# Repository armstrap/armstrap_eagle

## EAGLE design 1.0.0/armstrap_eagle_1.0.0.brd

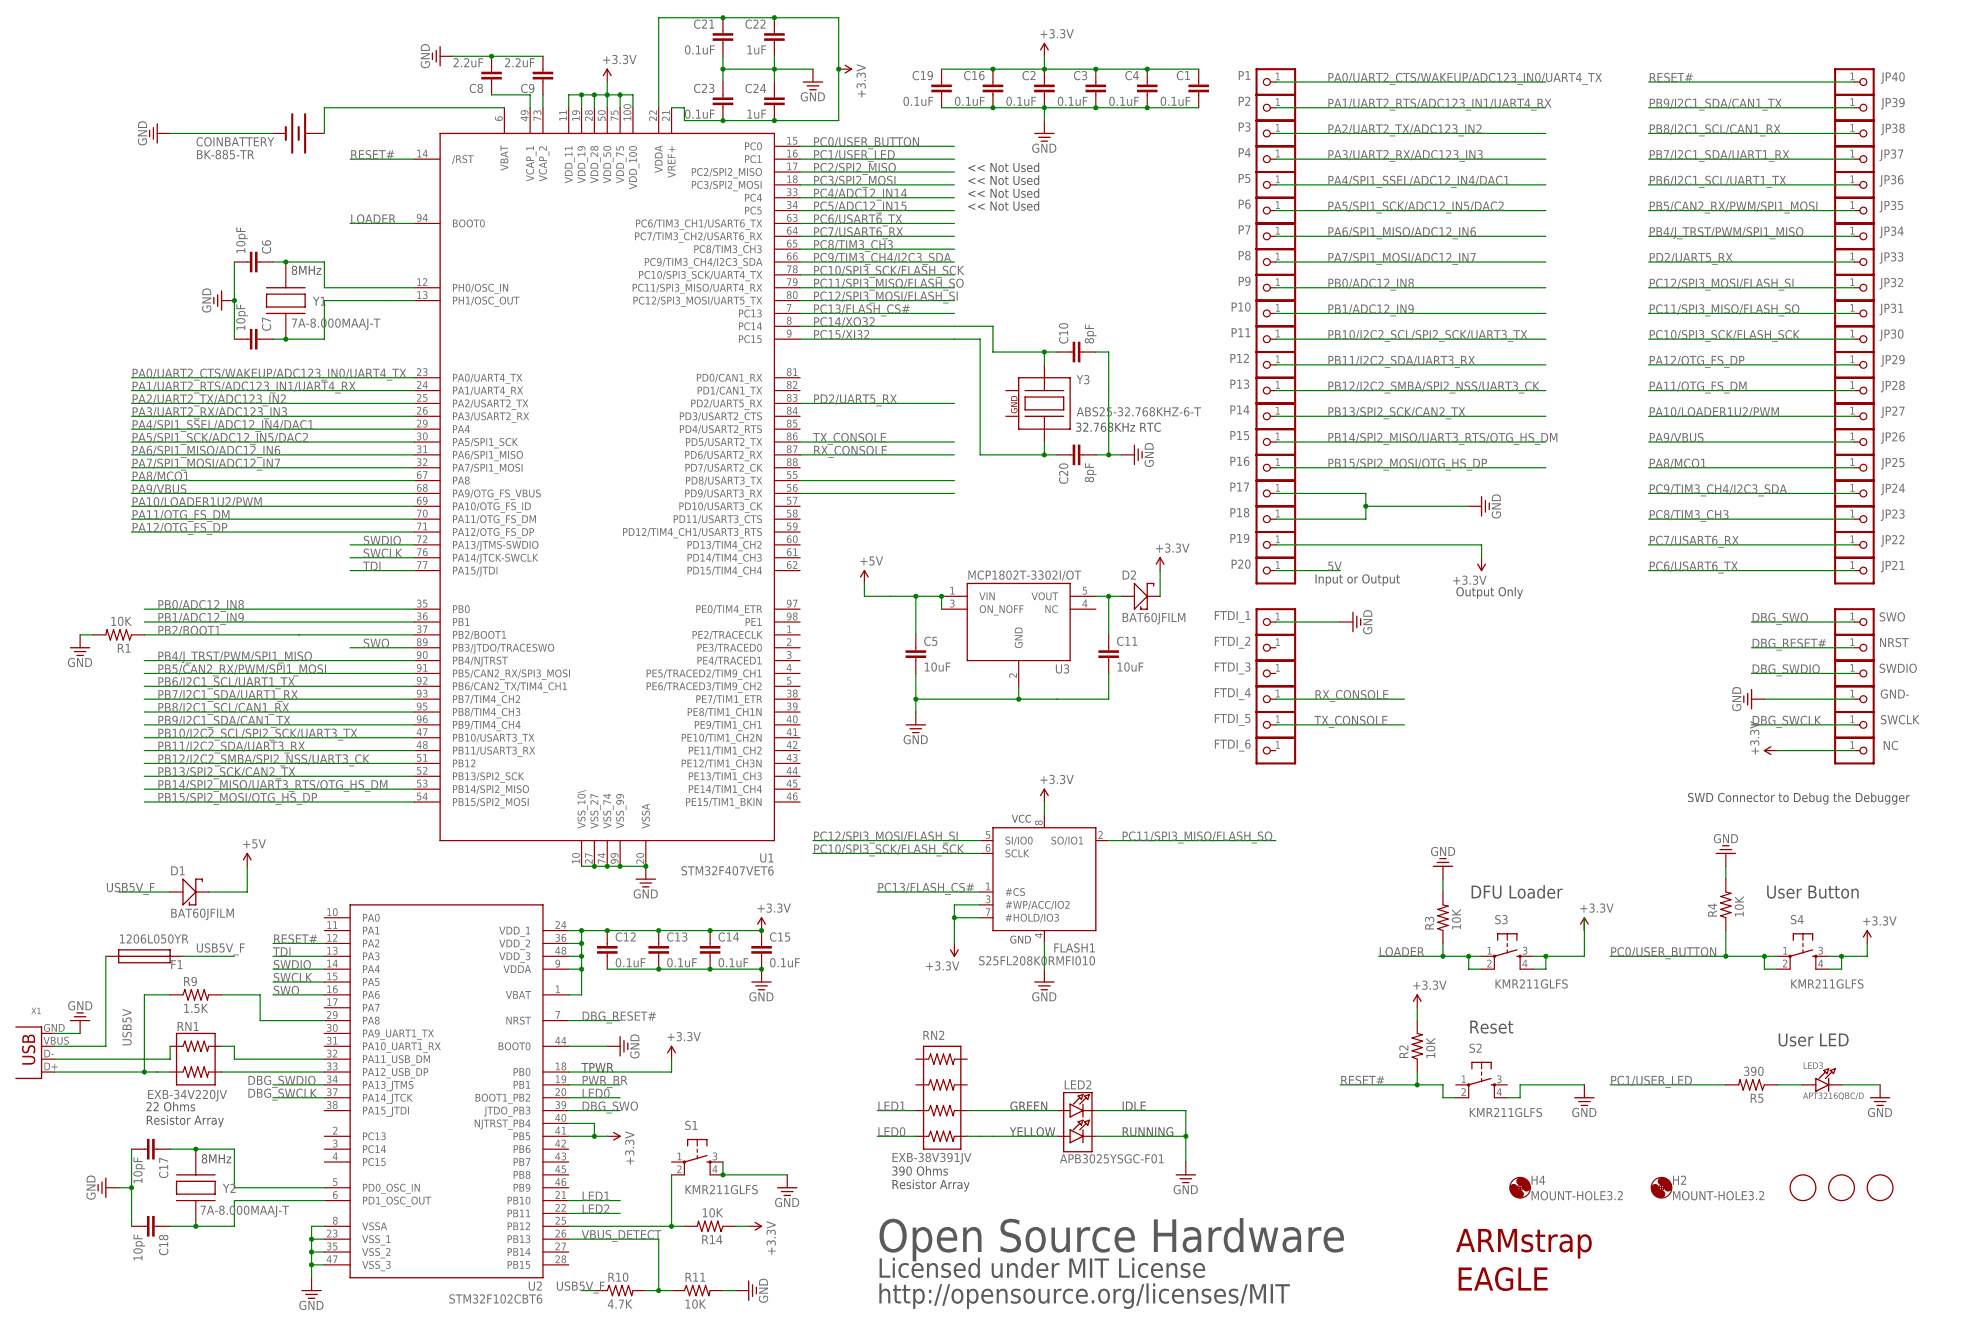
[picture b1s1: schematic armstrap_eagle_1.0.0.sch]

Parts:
C1, C2, C3, C4, C12, C13, C14, C15, C16, C19, C21, C23: 0.1uF; 0805
C5, C11: 10uF; 0805
C6, C7, C17, C18: 10pF; 0805
C8, C9: 2.2uF; 0805
C10, C20: 8pF; 0805
C22, C24: 1uF; 0805
COINBATTERY: BK-885-TR; BATTCON_12MM
D1, D2: BAT60JFILM; SOD-323
F1: 1206L050YR; PTC-1206
FID2, FID3, FID4: FIDUCIAL; FIDUCIAL_1MM
FLASH1: S25FL208K0RMFI010; SOIC-8-WIDE
FTDI_1, FTDI_2, FTDI_3, FTDI_4, FTDI_5, FTDI_6: PINHD-1X1; 1X01
GND-: PINHD-1X1; 1X01
H2, H4: MOUNT-HOLE3.2; 3,2
JP21, JP22, JP23, JP24, JP25, JP26, JP27, JP28, JP29, JP30, JP31, JP32, JP33, JP34, JP35, JP36, JP37, JP38, JP39, JP40: PINHD-1X1; 1X01
LED2: APB3025YSGC-F01; CHIPLED_1206-DUAL
LED3: APT3216QBC/D; CHIPLED_1206
NC: PINHD-1X1; 1X01
NRST: PINHD-1X1; 1X01
P1, P2, P3, P4, P5, P6, P7, P8, P9, P10, P11, P12, P13, P14, P15, P16, P17, P18, P19, P20: PINHD-1X1; 1X01
R1, R2, R3, R4, R11, R14: 10K; 0805
R5: 390; 0805
R9: 1.5K; 0805
R10: 4.7K; 0805
RN1: EXB-34V220JV; 0603-ARC2
RN2: EXB-38V391JV; 0603-ARC4
S1, S2, S3, S4: KMR211GLFS; KMR_SWITCH
SWCLK: PINHD-1X1; 1X01
SWDIO: PINHD-1X1; 1X01
SWO: PINHD-1X1; 1X01
U1: STM32F407VET6; LQFP100
U2: STM32F102CBT6; LQFP48
U3: MCP1802T-3302I/OT; MCP1802-SOT23
X1: 10033526-N3212MLF; USB-MB-S
Y1, Y2: 7A-8.000MAAJ-T; CRYSTAL-SMD-5.0MM-3.2MM-2
Y3: ABS25-32.768KHZ-6-T; CRYSTAL-SMD-32.768KHZ

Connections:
2: Y3.2
3.3V: C1.1, C2.1, C3.1, C4.1, C12.1, C13.1, C14.1, C15.1, C16.1, C19.1, C21.1, C22.1, C23.2, C24.2, D2.CATHODE (C), FLASH1.3 (#WP/ACC/IO2), FLASH1.7 (#HOLD/IO3), FLASH1.8 (VCC), NC.1, P19.1, R2.2, R14.1, S3.3, S3.4, S4.3, S4.4, U1.11 (VDD_11), U1.19 (VDD_19), U1.21 (VREF+), U1.22 (VDDA), U1.28 (VDD_28), U1.50 (VDD_50), U1.75 (VDD_75), U1.100 (VDD_100), U2.1 (VBAT), U2.9 (VDDA), U2.18 (PB0), U2.24 (VDD_1), U2.36 (VDD_2), U2.40 (NJTRST_PB4), U2.41 (PB5), U2.48 (VDD_3)
4: Y3.3 (4)
5V: C5.1, D1.CATHODE (C), P20.1, U3.1 (VIN), U3.3 (ON_NOFF)
DBG_RESET#: NRST.1, U2.7 (NRST)
DBG_SWCLK: SWCLK.1, U2.37 (PA14_JTCK)
DBG_SWDIO: SWDIO.1, U2.34 (PA13_JTMS)
DBG_SWO: SWO.1, U2.39 (JTDO_PB3)
GND: C1.2, C2.2, C3.2, C4.2, C5.2, C6.2, C7.2, C8.2, C9.2, C10.2, C11.2, C12.2, C13.2, C14.2, C15.2, C16.2, C17.2, C18.2, C19.2, C20.2, C21.2, C22.2, C23.1, C24.1, COINBATTERY.GND (-), FLASH1.4 (GND), FTDI_1.1, GND-.1, LED2.2, LED2.4, LED3.C, P17.1, P18.1, R1.2, R3.2, R4.2, R11.2, S1.3, S1.4, S2.4, U1.10 (VSS_10\), U1.20 (VSSA), U1.27 (VSS_27), U1.74 (VSS_74), U1.99 (VSS_99), U2.8 (VSSA), U2.23 (VSS_1), U2.35 (VSS_2), U2.44 (BOOT0), U2.47 (VSS_3), U3.2 (GND), X1.GND
LED0: RN2.4, U2.20 (BOOT1_PB2)
LED1: RN2.3, U2.21 (PB10)
LED2: U2.22 (PB11)
LOADER: R3.1, S3.1, S3.2, U1.94 (BOOT0)
unnamed: C7.1, U1.13 (PH1/OSC_OUT), Y1.2
unnamed: C9.1, U1.73 (VCAP_2)
unnamed: C17.1, U2.5 (PD0_OSC_IN), Y2.1
unnamed: R9.2, U2.29 (PA8)
unnamed: R9.1, RN1.2, X1.D+
unnamed: RN1.3, U2.33 (PA12_USB_DP)
unnamed: RN1.1, X1.D-
unnamed: RN1.4, U2.32 (PA11_USB_DM)
unnamed: C11.1, D2.ANODE (A), U3.5 (VOUT)
unnamed: C18.1, U2.6 (PD1_OSC_OUT), Y2.2
unnamed: R14.2, S1.2, U2.25 (PB12)
unnamed: LED3.A, R5.1
unnamed: LED2.3, RN2.6
unnamed: LED2.1, RN2.5
unnamed: C8.1, U1.49 (VCAP_1)
PA0/UART2_CTS/WAKEUP/ADC123_IN0/UART4_TX: P1.1, U1.23 (PA0/UART4_TX)
PA1/UART2_RTS/ADC123_IN1/UART4_RX: P2.1, U1.24 (PA1/UART4_RX)
PA2/UART2_TX/ADC123_IN2: P3.1, U1.25 (PA2/USART2_TX)
PA3/UART2_RX/ADC123_IN3: P4.1, U1.26 (PA3/USART2_RX)
PA4/SPI1_SSEL/ADC12_IN4/DAC1: P5.1, U1.29 (PA4)
PA5/SPI1_SCK/ADC12_IN5/DAC2: P6.1, U1.30 (PA5/SPI1_SCK)
PA6/SPI1_MISO/ADC12_IN6: P7.1, U1.31 (PA6/SPI1_MISO)
PA7/SPI1_MOSI/ADC12_IN7: P8.1, U1.32 (PA7/SPI1_MOSI)
PA8/MCO1: JP25.1, U1.67 (PA8)
PA9/VBUS: JP26.1, U1.68 (PA9/OTG_FS_VBUS)
PA10/LOADER1U2/PWM: JP27.1, U1.69 (PA10/OTG_FS_ID)
PA11/OTG_FS_DM: JP28.1, U1.70 (PA11/OTG_FS_DM)
PA12/OTG_FS_DP: JP29.1, U1.71 (PA12/OTG_FS_DP)
PB0/ADC12_IN8: P9.1, U1.35 (PB0)
PB1/ADC12_IN9: P10.1, U1.36 (PB1)
PB2/BOOT1: R1.1, U1.37 (PB2/BOOT1)
PB4/J_TRST/PWM/SPI1_MISO: JP34.1, U1.90 (PB4/NJTRST)
PB5/CAN2_RX/PWM/SPI1_MOSI: JP35.1, U1.91 (PB5/CAN2_RX/SPI3_MOSI)
PB6/I2C1_SCL/UART1_TX: JP36.1, U1.92 (PB6/CAN2_TX/TIM4_CH1)
PB7/I2C1_SDA/UART1_RX: JP37.1, U1.93 (PB7/TIM4_CH2)
PB8/I2C1_SCL/CAN1_RX: JP38.1, U1.95 (PB8/TIM4_CH3)
PB9/I2C1_SDA/CAN1_TX: JP39.1, U1.96 (PB9/TIM4_CH4)
PB10/I2C2_SCL/SPI2_SCK/UART3_TX: P11.1, U1.47 (PB10/USART3_TX)
PB11/I2C2_SDA/UART3_RX: P12.1, U1.48 (PB11/USART3_RX)
PB12/I2C2_SMBA/SPI2_NSS/UART3_CK: P13.1, U1.51 (PB12)
PB13/SPI2_SCK/CAN2_TX: P14.1, U1.52 (PB13/SPI2_SCK)
PB14/SPI2_MISO/UART3_RTS/OTG_HS_DM: P15.1, U1.53 (PB14/SPI2_MISO)
PB15/SPI2_MOSI/OTG_HS_DP: P16.1, U1.54 (PB15/SPI2_MOSI)
PC0/USER_BUTTON: R4.1, S4.1, S4.2, U1.15 (PC0)
PC1/USER_LED: R5.2, U1.16 (PC1)
PC2/SPI2_MISO: U1.17 (PC2/SPI2_MISO)
PC3/SPI2_MOSI: U1.18 (PC3/SPI2_MOSI)
PC4/ADC12_IN14: U1.33 (PC4)
PC5/ADC12_IN15: U1.34 (PC5)
PC6/USART6_TX: JP21.1, U1.63 (PC6/TIM3_CH1/USART6_TX)
PC7/USART6_RX: JP22.1, U1.64 (PC7/TIM3_CH2/USART6_RX)
PC8/TIM3_CH3: JP23.1, U1.65 (PC8/TIM3_CH3)
PC9/TIM3_CH4/I2C3_SDA: JP24.1, U1.66 (PC9/TIM3_CH4/I2C3_SDA)
PC10/SPI3_SCK/FLASH_SCK: FLASH1.6 (SCLK), JP30.1, U1.78 (PC10/SPI3_SCK/UART4_TX)
PC11/SPI3_MISO/FLASH_SO: FLASH1.2 (SO/IO1), JP31.1, U1.79 (PC11/SPI3_MISO/UART4_RX)
PC12/SPI3_MOSI/FLASH_SI: FLASH1.5 (SI/IO0), JP32.1, U1.80 (PC12/SPI3_MOSI/UART5_TX)
PC13/FLASH_CS#: FLASH1.1 (#CS), U1.7 (PC13)
PC14/XO32: C10.1, U1.8 (PC14), Y3.1
PC15/XI32: C20.1, U1.9 (PC15), Y3.4 (3)
PD2/UART5_RX: JP33.1, U1.83 (PD2/UART5_RX)
PWR_BR: U2.19 (PB1)
RESET#: JP40.1, R2.1, S2.2, U1.14 (/RST), U2.12 (PA2)
RX_CONSOLE: FTDI_4.1, U1.87 (PD6/USART2_RX)
SWCLK: U1.76 (PA14/JTCK-SWCLK), U2.15 (PA5)
SWDIO: U1.72 (PA13/JTMS-SWDIO), U2.14 (PA4)
SWO: U1.89 (PB3/JTDO/TRACESWO), U2.16 (PA6)
TDI: U1.77 (PA15/JTDI), U2.13 (PA3)
TX_CONSOLE: FTDI_5.1, U1.86 (PD5/USART2_TX)
USB5V: F1.1, X1.VBUS
USB5V_F: D1.ANODE (A), F1.2, R10.1
VBAT: COINBATTERY.PWR@2 (+), U1.6 (VBAT)
VBUS_DETECT: R10.2, R11.1, U2.26 (PB13)
XTAL3: C6.1, U1.12 (PH0/OSC_IN), Y1.1

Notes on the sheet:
ARMstrap
Open Source Hardware
Licensed under MIT License
http://opensource.org/licenses/MIT
GREEN
YELLOW
RUNNING
IDLE
SWD Connector to Debug the Debugger
Reset
DFU Loader
32.768KHz RTC
User Button
User LED
EAGLE
TPWR
Input or Output
Output Only
8MHz
390 Ohms Resistor Array
22 Ohms Resistor Array
<< Not Used

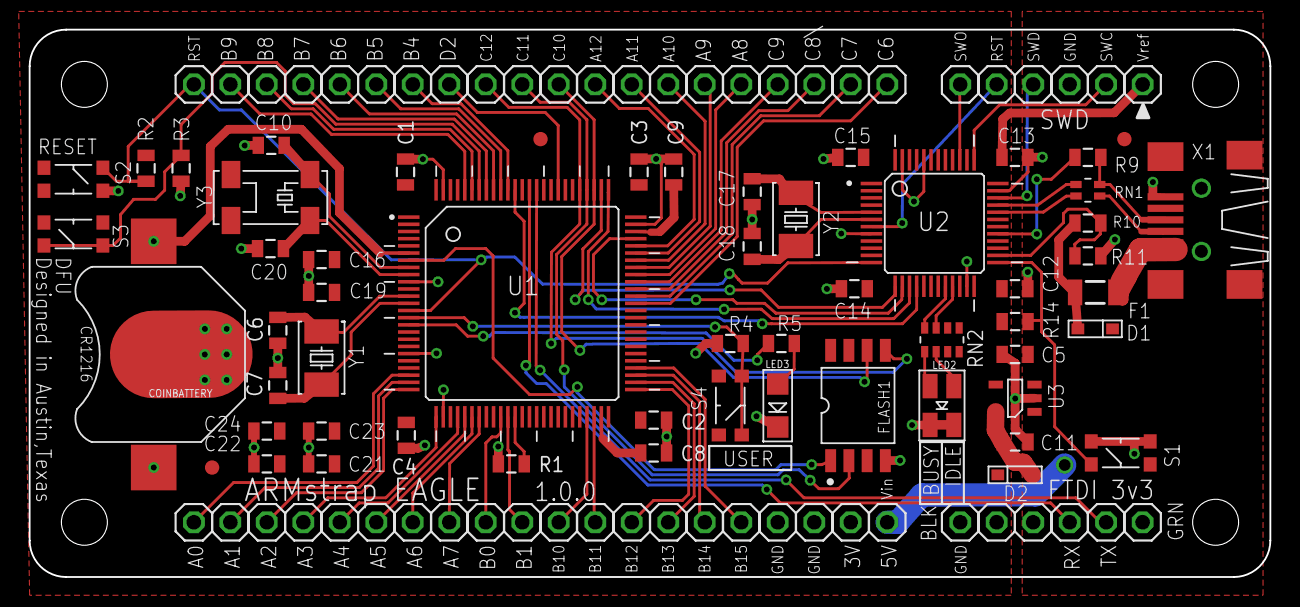
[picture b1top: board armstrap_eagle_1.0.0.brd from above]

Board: 2 copper layers, 86.4 x 38.1 mm, 112 parts (0 on the bottom side), 78 nets.

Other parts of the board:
H1, H3: MOUNT-HOLE3.2; 3,2

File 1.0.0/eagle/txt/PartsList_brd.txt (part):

Partlist

Exported from armstrap_eagle_1.0.0.brd at 12/7/14 10:09 PM

EAGLE Version 6.4.0 Copyright (c) 1988-2013 CadSoft

Assembly variant: 

Part        Value               Package                   Library  Position (inch)       Orientation

C1          0.1uF               0805                      vovtech  (1.03 1.11)           R90
C2          0.1uF               0805                      vovtech  (1.71 0.43)           R0
C3          0.1uF               0805                      vovtech  (1.67 1.11)           R90
C4          0.1uF               0805                      vovtech  (1.03206804 0.38820091) R270
C5          10uF                0805                      vovtech  (2.70055118 0.61)     R180
C6          10pF                0805                      vovtech  (0.68 0.676)          R270
C7          10pF                0805                      vovtech  (0.68 0.525)          R90
C8          2.2uF               0805                      vovtech  (1.71 0.34)           R0
C9          2.2uF               0805                      vovtech  (1.765 1.11)          R90
C10         8pF                 0805                      vovtech  (0.662 1.183)         R180
C11         10uF                0805                      vovtech  (2.70055118 0.37)     R0
C12         0.1uF               0805                      vovtech  (2.7 0.79)            R0
C13         0.1uF               0805                      vovtech  (2.7 1.15)            R0
C14         0.1uF               0805                      vovtech  (2.26 0.79)           R180
C15         0.1uF               0805                      vovtech  (2.25 1.15)           R180
C16         0.1uF               0805                      vovtech  (0.8 0.87)            R180
C17         10pF                0805                      vovtech  (1.98 1.056)          R270
C18         10pF                0805                      vovtech  (1.98 0.906)          R90
C19         0.1uF               0805                      vovtech  (0.8 0.78)            R180
C20         8pF                 0805                      vovtech  (0.66 0.9)            R180
C21         0.1uF               0805                      vovtech  (0.8 0.31)            R180
C22         1uF                 0805                      vovtech  (0.65 0.31)           R180
C23         0.1uF               0805                      vovtech  (0.8 0.4)             R0
C24         1uF                 0805                      vovtech  (0.65 0.4)            R0
COINBATTERY BK-885-TR           BATTCON_12MM              vovtech  (0.34 0.61)           R90
D1          BAT60JFILM          SOD-323                   vovtech  (2.92 0.68)           R180
D2          BAT60JFILM          SOD-323                   vovtech  (2.70055118 0.28)     R0
F1          1206L050YR          PTC-1206                  vovtech  (2.92 0.78)           R180
FID2        FIDUCIAL            FIDUCIAL_1MM              vovtech  (3 1.2)               R0
FID3        FIDUCIAL            FIDUCIAL_1MM              vovtech  (0.5 0.3)             R0
FID4        FIDUCIAL            FIDUCIAL_1MM              vovtech  (1.4 1.2)             R0
FLASH1      S25FL208K0RMFI010   SOIC-8-WIDE               vovtech  (2.27 0.47)           R0
FTDI_1                          1X01                      pinhead  (2.55 0.15)           R0
FTDI_2                          1X01                      pinhead  (2.65 0.15)           R0
FTDI_3                          1X01                      pinhead  (2.75 0.15)           R0
FTDI_4                          1X01                      pinhead  (2.85 0.15)           R0
FTDI_5                          1X01                      pinhead  (2.95 0.15)           R0
FTDI_6                          1X01                      pinhead  (3.05 0.15)           R0
GND-                            1X01                      pinhead  (2.85 1.35)           R0
JP21                            1X01                      pinhead  (2.35 1.35)           R0
JP22                            1X01                      pinhead  (2.25 1.35)           R0
JP23                            1X01                      pinhead  (2.15 1.35)           R0
JP24                            1X01                      pinhead  (2.05 1.35)           R0
JP25                            1X01                      pinhead  (1.95 1.35)           R0
JP26                            1X01                      pinhead  (1.85 1.35)           R0
JP27                            1X01                      pinhead  (1.75 1.35)           R0
JP28                            1X01                      pinhead  (1.65 1.35)           R0
JP29                            1X01                      pinhead  (1.55 1.35)           R0
JP30                            1X01                      pinhead  (1.45 1.35)           R0
JP31                            1X01                      pinhead  (1.35 1.35)           R0
JP32                            1X01                      pinhead  (1.25 1.35)           R0
JP33                            1X01                      pinhead  (1.15 1.35)           R0
JP34                            1X01                      pinhead  (1.05 1.35)           R0
JP35                            1X01                      pinhead  (0.95 1.35)           R0
JP36                            1X01                      pinhead  (0.85 1.35)           R0
JP37                            1X01                      pinhead  (0.75 1.35)           R0
JP38                            1X01                      pinhead  (0.65 1.35)           R0
JP39                            1X01                      pinhead  (0.55 1.35)           R0
JP40                            1X01                      pinhead  (0.45 1.35)           R0
LED2        APB3025YSGC-F01     CHIPLED_1206-DUAL         vovtech  (2.5 0.47)            R90
LED3        APT3216QBC/D        CHIPLED_1206              vovtech  (2.05 0.47)           R90
NC                              1X01                      pinhead  (3.05 1.35)           R0
NRST                            1X01                      pinhead  (2.65 1.35)           R0
P1                              1X01                      pinhead  (0.45 0.15)           R0
P2                              1X01                      pinhead  (0.55 0.15)           R90
P3                              1X01                      pinhead  (0.65 0.15)           R90
P4                              1X01                      pinhead  (0.75 0.15)           R90
P5                              1X01                      pinhead  (0.85 0.15)           R90
P6                              1X01                      pinhead  (0.95 0.15)           R90
P7                              1X01                      pinhead  (1.05 0.15)           R90
P8                              1X01                      pinhead  (1.15 0.15)           R90
P9                              1X01                      pinhead  (1.25 0.15)           R90
P10                             1X01                      pinhead  (1.35 0.15)           R90
P11                             1X01                      pinhead  (1.45 0.15)           R90
P12                             1X01                      pinhead  (1.55 0.15)           R90
P13                             1X01                      pinhead  (1.65 0.15)           R90
P14                             1X01                      pinhead  (1.75 0.15)           R90
P15                             1X01                      pinhead  (1.85 0.15)           R90
P16                             1X01                      pinhead  (1.95 0.15)           R90
P17                             1X01                      pinhead  (2.05 0.15)           R90
P18                             1X01                      pinhead  (2.15 0.15)           R90
P19                             1X01                      pinhead  (2.25 0.15)           R90
P20                             1X01                      pinhead  (2.35 0.15)           R90
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
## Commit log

2014-12-08 Adding ARMstrap Eagle files

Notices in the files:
parts and their libraries:
vovtech: Licensing: CC v3.0 Share-Alike You are welcome to use this library for commercial purposes.
